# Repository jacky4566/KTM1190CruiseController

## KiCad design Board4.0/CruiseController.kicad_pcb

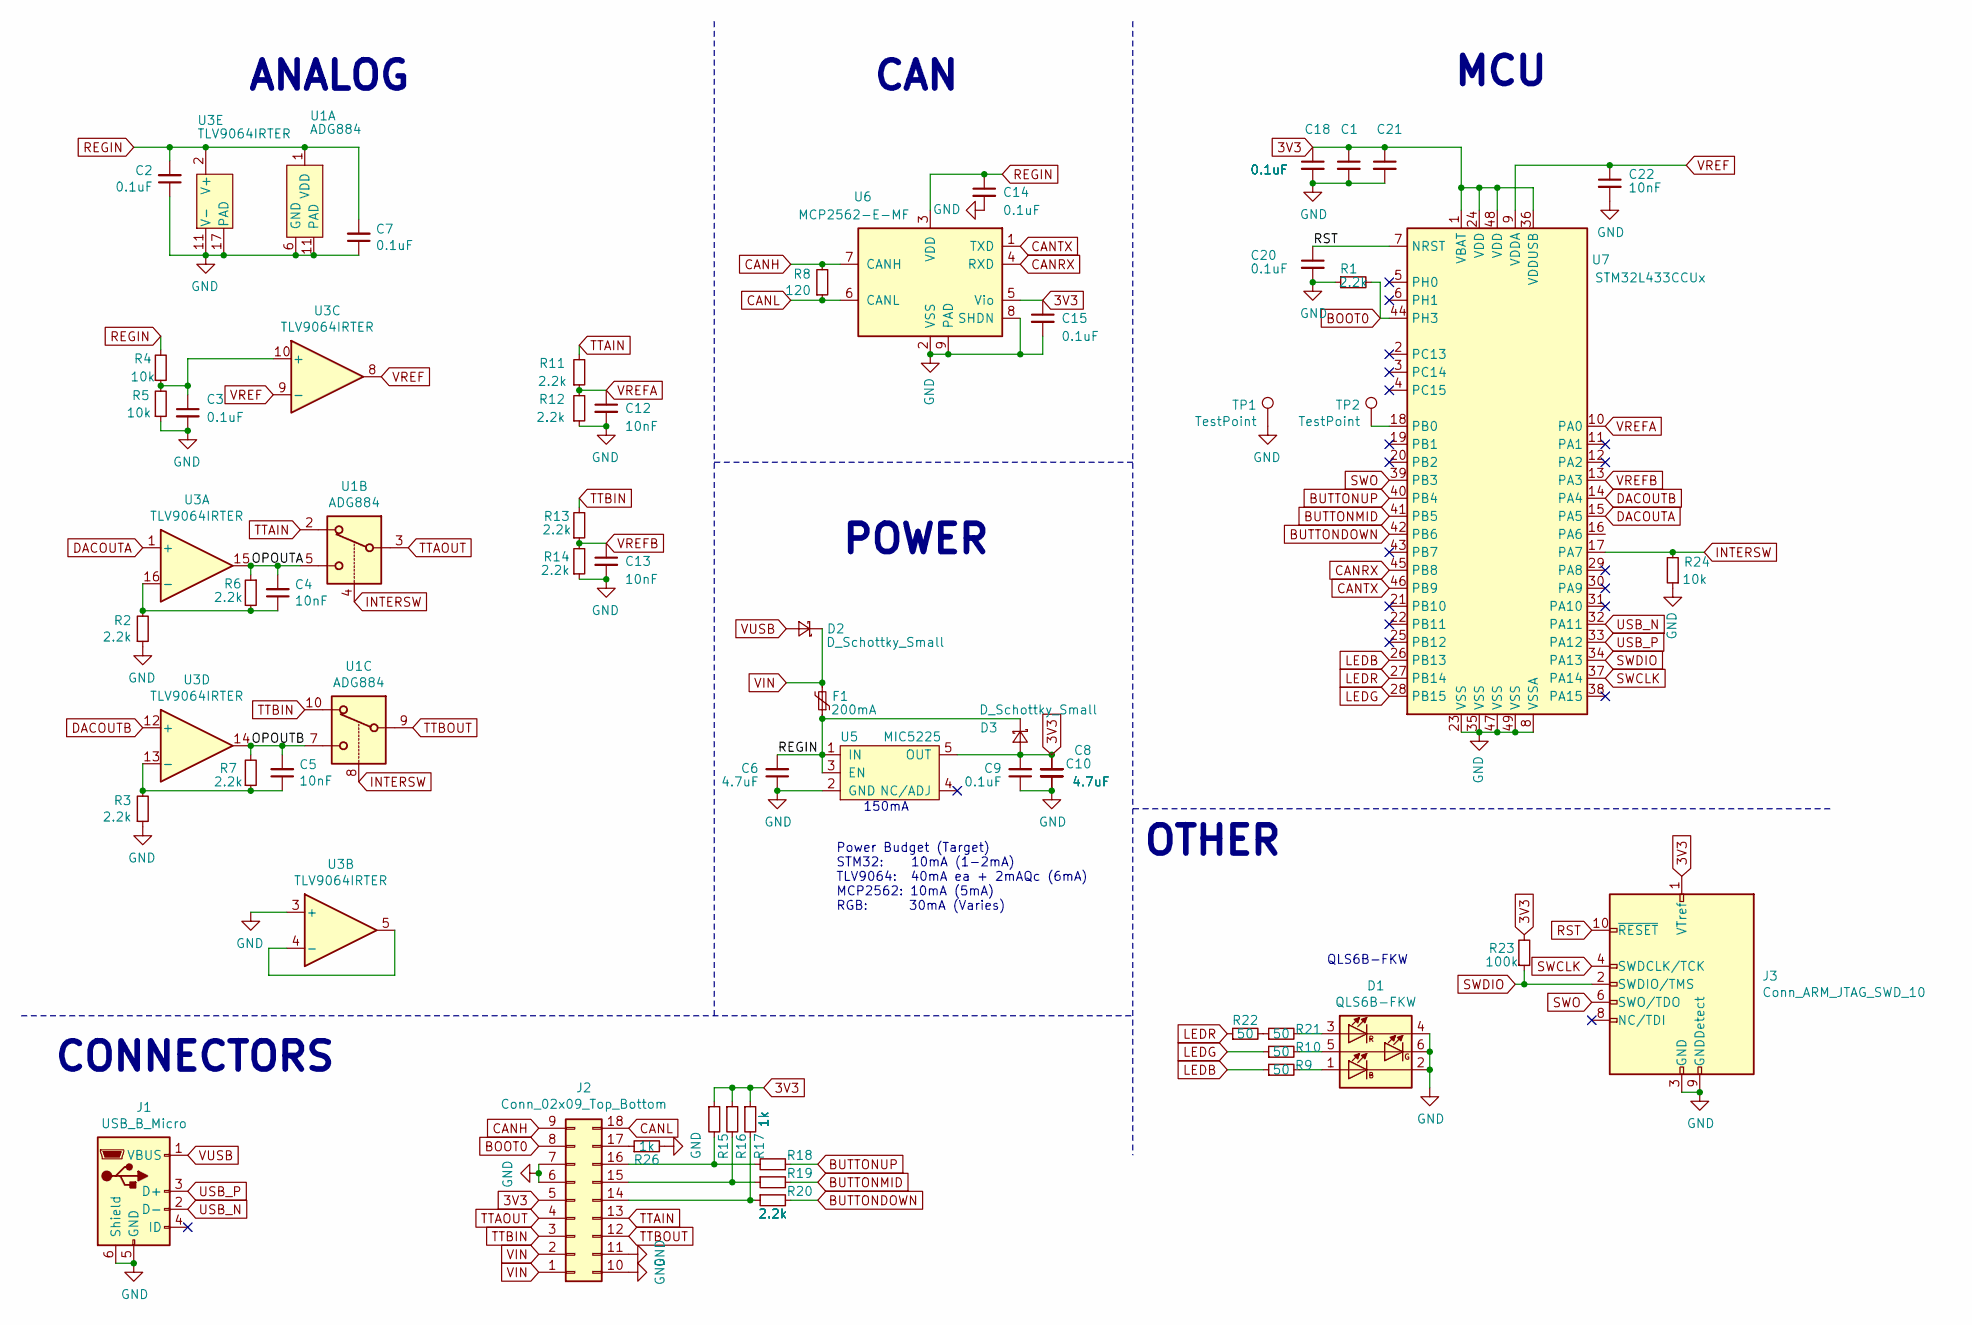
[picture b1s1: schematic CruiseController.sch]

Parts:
C1, C2, C3, C7, C9, C14, C15, C18, C20, C21: 0.1uF; C_0603_1608Metric
C4, C5, C12, C13, C22: 10nF; C_0603_1608Metric
C6, C8, C10: 4.7uF; C_0805_2012Metric
D1: QLS6B-FKW; LED_Cree-PLCC6_4.7x1.5mm
D2, D3: D_Schottky_Small; D_SOD-323
F1: 200mA; R_1206_3216Metric; Part 1206L020YR
J1: USB_B_Micro; CONN_2173157-3
J2: Conn_02x09_Top_Bottom; MX23A18NF1
J3: Conn_ARM_JTAG_SWD_10; PinHeader_2x05_P1.27mm_Vertical_SMD
R1, R2, R3, R6, R7, R11, R12, R13, R14, R18, R19, R20: 2.2k; R_0603_1608Metric
R4, R5, R24: 10k; R_0603_1608Metric
R8: 120; R_0805_2012Metric
R9, R10, R21, R22: 50; R_0603_1608Metric
R15, R16, R17, R26: 1k; R_0603_1608Metric
R23: 100k; R_0603_1608Metric
TP1: TestPoint; TestPoint_THTPad_D2.0mm_Drill1.0mm
TP2: TestPoint; TestPoint_Pad_1.5x1.5mm
U1: ADG884; Texas_S-PVSON-N10
U3: TLV9064IRTER; QFN-16-1EP_3x3mm_P0.5mm_EP1.7x1.7mm
U5: MIC5225; SOT-23-5
U6: MCP2562-E-MF; DFN-8-1EP_3x3mm_P0.65mm_EP1.55x2.4mm
U7: STM32L433CCUx; QFN-48-1EP_7x7mm_P0.5mm_EP5.6x5.6mm

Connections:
3V3: C1.1, C8.2, C9.2, C10.2, C15.1, C18.1, C21.1, D3.2 (A), J2.5, J3.1 (VTref), R15.1, R16.1, R17.1, R23.2, U5.5 (OUT), U6.5 (Vio), U7.1 (VBAT), U7.24 (VDD), U7.36 (VDDUSB), U7.48 (VDD)
/OPOUTA: C4.2, R6.1, U1.5, U3.15
/OPOUTB: C5.2, R7.2, U1.7, U3.14
BOOT0: J2.8, R1.2, U7.44 (PH3)
BUTTONDOWN: R20.2, U7.42 (PB6)
BUTTONMID: R19.2, U7.41 (PB5)
BUTTONUP: R18.1, U7.40 (PB4)
CANH: J2.9, R8.2, U6.7 (CANH)
CANL: J2.18, R8.1, U6.6 (CANL)
CANRX: U6.4 (RXD), U7.45 (PB8)
CANTX: U6.1 (TXD), U7.46 (PB9)
DACOUTA: U3.1 (+), U7.15 (PA5)
DACOUTB: U3.12 (+), U7.14 (PA4)
GND: C1.2, C2.1, C3.2, C6.1, C7.1, C8.1, C9.1, C10.1, C12.2, C13.2, C14.2, C15.2, C18.2, C20.2, C21.2, C22.2, D1.2 (KB), D1.4 (KR), D1.6 (KR), J1.5 (GND), J1.6 (Shield), J2.6, J2.7, J2.10, J2.11, J3.3 (GND), J3.5 (GND), J3.9 (GNDDetect), R1.1, R2.1, R3.1, R5.1, R12.1, R14.1, R24.1, R26.2, TP1.1, U1.6 (GND), U1.11 (PAD), U3.3 (+), U3.11 (V-), U3.17 (PAD), U5.2 (GND), U6.2 (VSS), U6.8 (SHDN), U6.9 (PAD), U7.8 (VSSA), U7.23 (VSS), U7.35 (VSS), U7.47 (VSS), U7.49 (VSS)
INTERSW: R24.2, U1.4, U1.8, U7.17 (PA7)
LEDB: R9.1, U7.26 (PB13)
LEDG: R10.1, U7.28 (PB15)
LEDR: R22.1, U7.27 (PB14)
unnamed: C3.1, R4.1, R5.2, U3.10 (+)
unnamed: C4.1, R2.2, R6.2, U3.16 (-)
unnamed: C5.1, R3.2, R7.1, U3.13 (-)
unnamed: D1.1 (AB), R9.2
unnamed: D1.3 (AR), R21.2
unnamed: D1.5 (AG), R10.2
unnamed: J2.14, R17.2, R20.1
unnamed: J2.15, R16.2, R19.1
unnamed: J2.16, R15.2, R18.2
unnamed: J2.17, R26.1
unnamed: R21.1, R22.2
unnamed: TP2.1, U7.18 (PB0)
unnamed: U3.4 (-), U3.5
REGIN: C2.2, C6.2, C7.2, C14.1, D3.1 (K), F1.1, R4.2, U1.1 (VDD), U3.2 (V+), U5.1 (IN), U5.3 (EN), U6.3 (VDD)
RST: C20.1, J3.10 (~RESET~), U7.7 (NRST)
SWCLK: J3.4 (SWDCLK/TCK), U7.37 (PA14)
SWDIO: J3.2 (SWDIO/TMS), R23.1, U7.34 (PA13)
SWO: J3.6 (SWO/TDO), U7.39 (PB3)
TTAIN: J2.13, R11.2, U1.2
TTAOUT: J2.4, U1.3
TTBIN: J2.3, R13.2, U1.10
TTBOUT: J2.12, U1.9
USB_N: J1.2 (D-), U7.32 (PA11)
USB_P: J1.3 (D+), U7.33 (PA12)
VIN: D2.1 (K), F1.2, J2.1, J2.2
VREF: C22.1, U3.8, U3.9 (-), U7.9 (VDDA)
VREFA: C12.1, R11.1, R12.2, U7.10 (PA0)
VREFB: C13.1, R13.1, R14.2, U7.13 (PA3)
VUSB: D2.2 (A), J1.1 (VBUS)

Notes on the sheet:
150mA
Power Budget (Target) STM32: 10mA (1-2mA) TLV9064: 40mA ea + 2mAQc (6mA) MCP2562: 10mA (5mA) RGB: 30mA (Varies)
ANALOG
POWER
CAN
MCU
CONNECTORS
OTHER
QLS6B-FKW

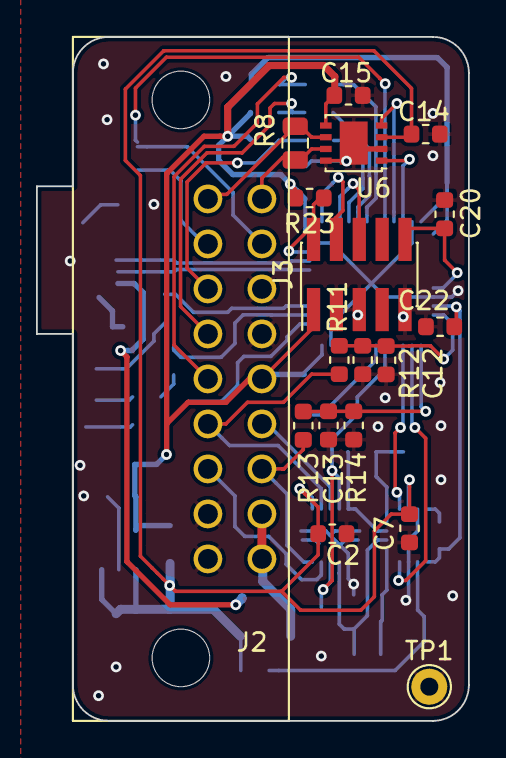
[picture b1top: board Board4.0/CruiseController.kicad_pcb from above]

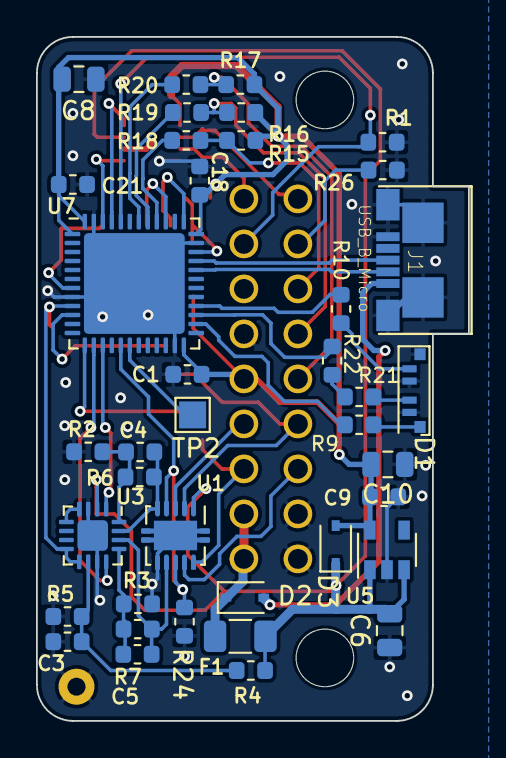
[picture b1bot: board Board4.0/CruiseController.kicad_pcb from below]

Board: 2 copper layers, 24.0 x 38.0 mm, 57 parts (39 on the bottom side), 47 nets.

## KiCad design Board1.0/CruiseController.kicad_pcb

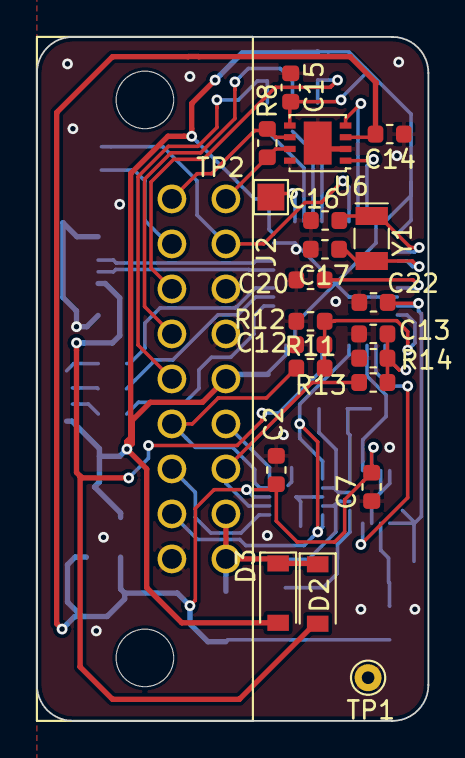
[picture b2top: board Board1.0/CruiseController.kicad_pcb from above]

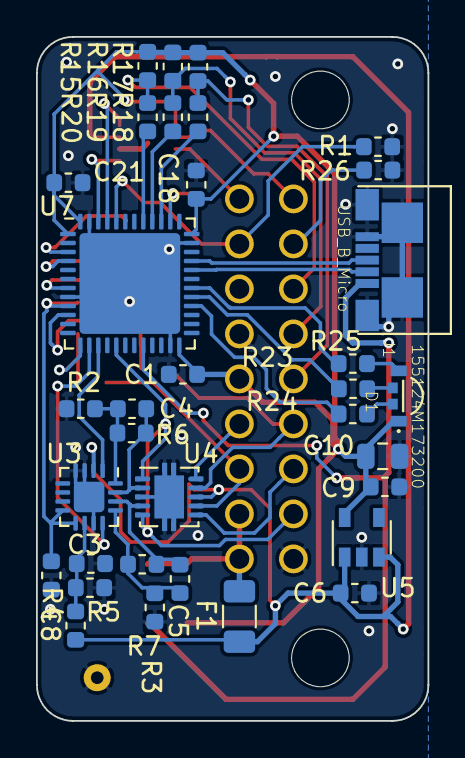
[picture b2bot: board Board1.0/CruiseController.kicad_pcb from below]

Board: 2 copper layers, 21.8 x 38.0 mm, 56 parts (34 on the bottom side), 44 nets.

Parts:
C1, C2, C3, C7, C9, C14, C15, C18, C20, C21: 0.1uF; C_0603_1608Metric
C4, C5, C12, C13, C22: 10nF; C_0603_1608Metric
C6, C8: 1uF; C_0603_1608Metric
C10: 4.7uF; C_0805_2012Metric
C16, C17: 8pF; C_0603_1608Metric
D1: 155124M173200; LED_155124M173200
D2, D3: D_Schottky_Small; D_SOD-123
F1: 200mA; R_1206_3216Metric
J1: USB_B_Micro; CONN_2173157-3
J2: Conn_02x09_Top_Bottom; MX23A18NF1
R1, R2, R3, R4, R5, R6, R7, R11, R12, R13, R14: 10k; R_0603_1608Metric
R8: 120; R_0603_1608Metric
R15, R16, R17, R26: 1k; R_0603_1608Metric
R18, R19, R20: 2.2k; R_0603_1608Metric
R23, R24: 27; R_0603_1608Metric
R25: 75; R_0603_1608Metric
TP1: TestPoint; TestPoint_THTPad_D1.5mm_Drill0.7mm
TP2: TestPoint; TestPoint_Pad_1.5x1.5mm
U3: TLV9064IRTER; QFN-16-1EP_3x3mm_P0.5mm_EP1.7x1.7mm
U4: TS5A23157RSER; Texas_S-PVSON-N10
U5: MIC5225; SOT-23-5
U6: MCP2562-E-MF; DFN-8-1EP_3x3mm_P0.65mm_EP1.55x2.4mm
U7: STM32L433CCUx; QFN-48-1EP_7x7mm_P0.5mm_EP5.6x5.6mm
Y1: 32.768; Crystal_SMD_G8-2Pin_3.2x1.5mm

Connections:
3V3: C1.1, C9.2, C10.2, C15.1, C18.1, C21.1, D1.1, D3.2, J2.5, R15.2, R16.2, R17.2, U5.5, U6.5, U7.1, U7.24, U7.36, U7.48
/RST: C20.1, U7.7
/USB_N: J1.2, U7.32
/USB_P: J1.3, U7.33
BOOT0: J2.8, R1.2, U7.44
BUTTONDOWN: R20.2, U7.39
BUTTONMID: R19.2, U7.40
BUTTONUP: R18.1, U7.41
CANH: J2.9, R8.2, U6.7
CANL: J2.18, R8.1, U6.6
CANRX: U6.4, U7.45
CANTX: U6.1, U7.46
DACOUTA: U3.1, U7.15
DACOUTB: U3.12, U7.14
GND: C1.2, C2.1, C3.2, C6.1, C7.1, C8.2, C9.1, C10.1, C12.2, C13.2, C14.2, C15.2, C16.1, C17.1, C18.2, C20.2, C21.2, C22.2, J1.5, J1.6, J2.6, J2.7, J2.10, R1.1, R2.1, R3.1, R5.1, R12.1, R14.1, R26.2, TP1.1, U3.3, U3.4, U3.11, U3.17, U4.3, U4.11, U5.2, U6.2, U6.8, U6.9, U7.8, U7.23, U7.35, U7.47, U7.49
INTERSW: J2.11, U4.1, U4.5, U7.17
LED1: R24.1, U7.28
LED2: R23.1, U7.29
LED3: R25.1, U7.30
unnamed: C3.1, R4.1, R5.2, U3.10
unnamed: C4.1, R2.2, R6.2, U3.16
unnamed: C4.2, R6.1, U3.15, U4.2
unnamed: C5.1, R3.2, R7.1, U3.13
unnamed: C5.2, R7.2, U3.14, U4.4
unnamed: C16.2, U7.3, Y1.1
unnamed: C17.2, U7.4, Y1.2
unnamed: D1.2, R24.2
unnamed: D1.3, R23.2
unnamed: D1.4, R25.2
unnamed: J2.14, R17.1, R20.1
unnamed: J2.15, R16.1, R19.1
unnamed: J2.16, R15.1, R18.2
unnamed: J2.17, R26.1
unnamed: TP2.1, U7.38
REGIN: C2.2, C6.2, C7.2, C14.1, F1.1, R4.2, U3.2, U4.8, U5.1, U5.3, U6.3
TTAIN: J2.13, R11.2, U4.9
TTAOUT: J2.4, U4.10
TTBIN: J2.3, R13.2, U4.7
TTBOUT: J2.12, U4.6
VIN: D2.1, D3.1, F1.2, J2.1, J2.2
VREF: C8.1, C22.1, U3.8, U3.9, U7.9
VREFA: C12.1, R11.1, R12.2, U7.10
VREFB: C13.1, R13.1, R14.2, U7.13
VUSB: D2.2, J1.1, U7.20

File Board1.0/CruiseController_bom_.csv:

Component,Description,Part,References,Value,Footprint,Quantity Per PCB,Digikey P/N,Cost @10,Expanded cost
1,"Unpolarized capacitor, small symbol",C_Small,C1 C2 C3 C7 C9 C14 C15 C18 C20 C21,0.1uF,C_0603_1608Metric,10,1276-6582-1-ND, $0.0254 , $0.2540 
2,"Unpolarized capacitor, small symbol",C_Small,C4 C5 C12 C13 C22,10nF,C_0603_1608Metric,5,1276-6531-1-ND, $0.0490 , $0.2450 
3,"Unpolarized capacitor, small symbol",C_Small,C6 C8,1uF,C_0603_1608Metric,2,1276-6617-1-ND, $0.1192 , $0.2384 
4,"Unpolarized capacitor, small symbol",C_Small,C10,4.7uF,C_0805_2012Metric,1,1276-6783-1-ND, $0.3600 , $0.3600 
5,"Unpolarized capacitor, small symbol",C_Small,C16 C17,8pF,C_0603_1608Metric,2,1276-6519-1-ND, $0.2360 , $0.4720 
6,,155124M173200-VeridianDesigns,D1,155124M173200,LED_155124M173200,1,732-11414-1-ND, $0.5862 , $0.5862 
7,"Schottky diode, small symbol",D_Schottky_Small,D2 D3,D_Schottky_Small,D_SOD-123,2,497-17154-1-ND, $0.2362 , $0.4724 
8,"Resettable fuse, polymeric positive temperature coefficient, small symbol",Polyfuse_Small,F1,200mA,R_1206_3216Metric,1,F2109TR-ND, $0.5071 , $0.5071 
9,"Generic connector, double row, 02x09, top/bottom pin numbering scheme (row 1: 1...pins_per_row, row2: pins_per_row+1 ... num_pins), script generated (kicad-library-utils/schlib/autogen/connector/)",Conn_02x09_Top_Bottom,J2,Conn_02x09_Top_Bottom,MX23A18NF1,1,670-2462-ND, $10.3800 , $10.3800 
10,USB Micro Type B connector,USB_B_Micro,J1,USB_B_Micro,CONN_2173157-3,1,A124356TR-ND, $4.9780 , $4.9780 
11,"Resistor, small symbol",R_Small,R1 R2 R3 R4 R5 R6 R7 R11 R12 R13 R14,10k,R_0603_1608Metric,11,P10KDBCT-ND, $0.1793 , $1.9723 
12,"Resistor, small symbol",R_Small,R8,120,R_0603_1608Metric,1,P120BZCT-ND, $0.1450 , $0.1450 
13,"Resistor, small symbol",R_Small,R15 R16 R17 R26,1k,R_0603_1608Metric,4,CR0603-JW-102ELFCT-ND, $0.0210 , $0.0840 
14,"Resistor, small symbol",R_Small,R18 R19 R20,2.2k,R_0603_1608Metric,3,P2.2KGCT-ND, $0.0660 , $0.1980 
15,"Resistor, small symbol",R_Small,R23 R24,27,R_0603_1608Metric,2,P27.00BYCT-ND, $0.1940 , $0.3880 
16,"Resistor, small symbol",R_Small,R25,75,R_0603_1608Metric,1,P75.0HCT-ND, $0.0870 , $0.0870 
17,"High-Speed CAN Transceiver, 1Mbps, 5V supply, Vio pin, -40C to +125C, DFN8 package",MCP2562-E-MF,U6,MCP2562-E-MF,DFN-8-1EP_3x3mm_P0.65mm_EP1.55x2.4mm,1,MCP2562-E/MF-ND, $1.4200 , $1.4200 
18,,MIC5225,U5,MIC5225,SOT-23-5,1,576-2980-1-ND, $0.6000 , $0.6000 
19,"ARM Cortex-M4 MCU, 256KB flash, 64KB RAM, 80MHz, 1.71-3.6V, 38 GPIO, UFQFPN-48",STM32L433CCUx,U7,STM32L433CCUx,QFN-48-1EP_7x7mm_P0.5mm_EP5.6x5.6mm,1,497-16580-ND, $7.8280 , $7.8280 
20,,TLV9064IRTER-VeridianDesigns,U3,TLV9064IRTER,QFN-16-1EP_3x3mm_P0.5mm_EP1.7x1.7mm,1,296-51830-1-ND, $2.1660 , $2.1660 
21,,TS5A23157RSER-VeridianDesigns,U4,TS5A23157RSER,Texas_S-PVSON-N10,1,296-21919-2-ND, $1.0970 , $1.0970 
22,Two pin crystal,Crystal,Y1,32.768,Crystal_SMD_G8-2Pin_3.2x1.5mm,1,535-9537-1-ND, $1.2150 , $1.2150 
,,,,,,,,,
,,Bare Board,,,,1,, $3.1600 , $3.1600 
,,Assembly,,,,1,, $15.0000 , $15.0000 
,,Assembly shipping,,,,1,, $1.0000 , $1.0000 
,,,,,,,,,
Connectors,,,,,,,,,
1,,,,HM-4P,,1,, $3.0100 , $3.0100 
2,,,,MT-6P-2,,2,, $3.1300 , $6.2600 
3,,,,MT-6S-2,,3,, $2.0600 , $6.1800 
4,,,CONN SOCKET HOUSING 18POS,MX23A18SF1,,1,670-2463-ND, $7.28 , $7.28 
4a,,,CONN SOCKET 16-22AWG CRIMP TIN,M23S05K351,,18,670-1682-1-ND,0.153, $2.75 
,,,,,,,,,
Wire,,,,20 AWG,,4,, $1.0000 , $4.0000 
Seliving,,,,Orange!,,4,, $0.2500 , $1.0000 
Case and Epoxy,,,,,,1,, $2.0000 , $2.0000 
,,,,,,,,,
,,,,,,,,,
KTM switches,,,,,,1,, $100.0000 , $100.0000 
,,,,,,,,,
,,,,,,,,,
,,,,,,,,, $187.332

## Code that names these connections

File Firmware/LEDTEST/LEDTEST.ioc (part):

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Mcu.Name=STM32L433C(B-C)Ux
Mcu.Package=UFQFPN48
Mcu.UserName=STM32L433CCUx
PA0.GPIOParameters=GPIO_Label
PA0.GPIO_Label=ADC_VREFA
PA0.Signal=ADCx_IN5
PA11.Mode=Device
PA11.Signal=USB_DM
PA12.Mode=Device
PA12.Signal=USB_DP
PA3.GPIOParameters=GPIO_Label
PA3.GPIO_Label=ADC_VREFB
PA3.Signal=ADCx_IN8
PA4.Signal=COMP_DAC11_group
PA5.Signal=COMP_DAC12_group
PB13.GPIOParameters=GPIO_Label
PB13.GPIO_Label=LEDB
PB13.Signal=GPIO_Output
PB14.GPIOParameters=GPIO_Label
PB14.GPIO_Label=LEDR
PB14.Signal=GPIO_Output
PB15.GPIOParameters=GPIO_Label
PB15.GPIO_Label=LEDG
PB15.Signal=GPIO_Output
RCC.HSE_VALUE=8000000
RCC.SYSCLKFreq_VALUE=64000000
RCC.SYSCLKSource=RCC_SYSCLKSOURCE_PLLCLK
board=custom

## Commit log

2019-12-08 Updated BOM
2019-12-08 Readability
2019-12-08 Data Sheet organize
2019-12-09 Board V2
2019-12-09 V2 replace LED
2019-12-10 Update V2
    increase usb area
2019-12-10 Added canbus library for stm32
2019-12-12 Update Can library
2019-12-14 testing dac dma. work on V01
2019-12-17 write new can test, update main code
2019-12-19 udpate v2 pcb
2019-12-19 pcb v2
2019-12-19 update pcbv2
2019-12-22 submit board 2 for quote
2019-12-23 update pcb v2
2019-12-27 start pcb v3
2020-01-05 Draw v3
2020-01-10 add swtich templates
2020-01-10 fix LED PWM pins
2020-03-20 Update v3
2020-03-20 Update Cabling
2020-06-09 Geber Files
2020-09-22 Board 4.0
2020-09-22 Switch to STM32CUBEIDE
2020-11-05 Update images
2020-11-22 Add 3d files
